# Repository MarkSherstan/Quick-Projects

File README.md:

# [Wiki](https://github.com/MarkSherstan/Quick-Projects/wiki)
Check out the [Wiki](https://github.com/MarkSherstan/Quick-Projects/wiki) for full details on this repository. 

If you plan on working offline consider cloning the wiki locally:
```
git clone https://github.com/MarkSherstan/Quick-Projects.wiki.git
```

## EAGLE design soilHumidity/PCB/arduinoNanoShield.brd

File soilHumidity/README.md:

# Soil Humidity Classifier for Home Plants
Program for determining the soil humidity levels in various house hold plants.

Also using the project to test the basic functionality of PlatformIO instead of Arduino IDE.

## Usage
Build and upload with PlatformIO or copy and paste `\src\main.cpp` excluding the `#include <Arduino.h>` header into Arduino IDE and compile as normal.

The 7 segment display values correspond to the relative humidity. For example 1 indicates 0-10% relative humidity, 2 indicates 10-20% relative humidity, etc... For greater than 90% relative humidity the decimal point will flash.

## Specs and Data Sheets
Sensor purchased from Banggood and came with the following information:

* Supply voltage: 3.3V or 5V
* Operating current: less than 20mA
* Output voltage: 0-2.3V (2.3V is completely immersed in water voltage value),
* 5V power supply, the greater the humidity, the greater the output voltage.
* Sensor type: Analog Output

## Case
The top of the case was modified from [this](https://www.thingiverse.com/thing:994827) model on Thingiverse. CAD files can be found in the `case` directory.  

## Wiring schematic

## Cover Photo

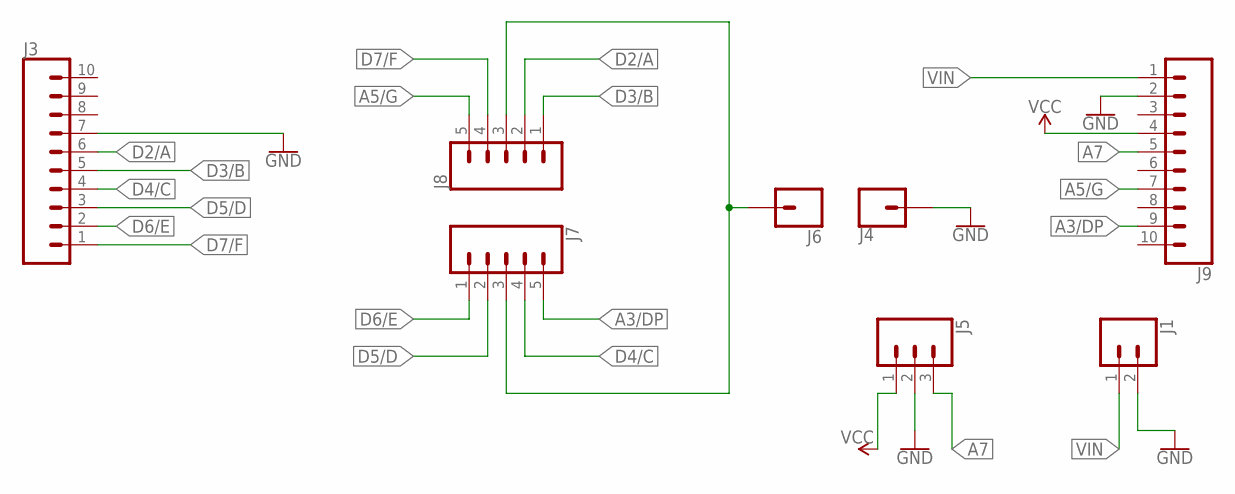
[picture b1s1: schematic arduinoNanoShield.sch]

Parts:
J1: CONN_02; 1X02
J3, J9: CONN_10"; 1X10
J4, J6: CONN_01; 1X01
J5: CONN_03; 1X03
J7, J8: CONN_05; 1X05

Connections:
A3/DP: J7.5, J9.9
A5/G: J8.5, J9.7
A7: J5.3, J9.5
D2/A: J3.6, J8.2
D3/B: J3.5, J8.1
D4/C: J3.4, J7.4
D5/D: J3.3, J7.2
D6/E: J3.2, J7.1
D7/F: J3.1, J8.4
GND: J1.2, J3.7, J4.1, J5.2, J9.2
unnamed: J6.1, J7.3, J8.3
VCC: J5.1, J9.4
VIN: J1.1, J9.1

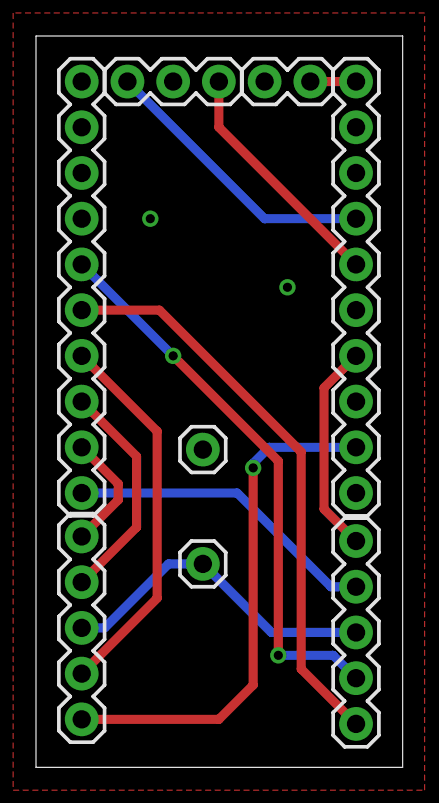
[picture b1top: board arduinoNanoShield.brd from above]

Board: 2 copper layers, 20.4 x 40.6 mm, 8 parts (0 on the bottom side), 13 nets.

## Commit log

2019-01-21 Commit PlatformIO root files
2019-01-21 Wrote initial framework of arduino sketch.
2019-01-21 Update README(s)
2019-01-21 Add second sensor and average results
2019-01-22 Fixed LED's from always staying on once activated by if statment.
2019-01-23 Initial commit wiring diagram
2019-01-23 Use one sensor and one LED and vary blinking speeds.
2019-01-26 Changed code to use 7 segment display instead of flashing LED
2019-01-26 Update wiring diagram for 7 seg display.
2019-01-26 Commit CAD files.
2019-01-26 Add cover photos
2019-01-26 Read add cover photos - HEIC format.
2019-01-26 Compress file size for cover photos.
2019-01-26 Remove HEIC, export .png, resize cover photos.
2019-01-26 Update README
    Change to HTML formatting from ![]()
2019-01-26 Update README
    Change from ![]() to HTML
2019-01-26 Change aspect ratio of cover photos
2019-01-27 Changed output for greater than 100% to be just a dot.
2019-02-15 Initial commit of sensor project code.
2019-02-18 Designed quick PCB to test othermill pro in engg garage.
2019-03-01 Initial commit for Arduino ESC calibration
2019-03-01 Initial commit of Arduino servo control using serial port.
2019-03-03 Initial commit for detecting mouse location to set up automater.
2019-03-04 Changed clicks to tabs for speed increase
2019-03-04 Created function for multiple entries
2019-03-04 Initial commit of README
2019-03-08 Initial commit real time plotter .m function.
2019-03-27 MATLAB and Arduino serial port communication. 45-50 Hz with MEGA2560.
2019-04-30 Initial commit - Slider for HSV colorspace and masking.
2019-05-01 Upload some test data
2019-05-02 Update background detection algorithm and laser tracking.
2019-05-02 Add the updated background and laser tracking to RPi code.
2019-05-02 Initial commit of C++ serial port reading.
2019-05-02 Initial commit of analog thermistor sensor.
2019-05-02 Initial commit of ultrasonic sensor
2019-05-17 Initial commit serialPython.py
2019-05-17 Initial commit C++ files for serial port.
2019-05-17 Initial commit arduinoSerial.ino
2019-05-17 Initial commit serialMatlab.m
2019-05-17 Commit MATLAB serial port reading (2 methods).
2019-05-17 Formatting update.
2019-06-01 Transition to windows and make user enter after every entry.
2019-09-30 Initial commit FSR sketch
2019-09-30 Add FSR-400 data sheet
2019-09-30 HX711 amplifier and load cell.
2019-09-30 Add README
2019-10-11 Fill out README
2019-10-12 Commit JSON parsing and dataframe work
2019-10-12 Commit gitignore for PNG's
2019-10-12 Tune some OCR and image processing properties.
2019-10-13 Only use one screen shot. Get rid of other functions for img processing.
2019-10-13 Make corresponding changes to JSON class
2019-10-13 Added comparison dataFrame columns and tidy up a few functions.
2019-10-13 Added some error handling.
2019-10-13 Commit example data and GAME_MASTER from october 11, 2019.
2019-10-13 Add file extension
2019-10-18 Initialize readme
2019-10-18 Commit calibration directory.
2019-10-18 Add first few functions for marker gen and calibration data gen.
2019-10-18 Commit calibration and retrieval function
2019-10-18 Added real time tracking.
2019-10-19 Add gitignore for images and pickles
2019-10-19 Debuging and testing.
2019-10-19 Commit main arduino sketch for servo control.
2019-10-19 Commit serial grabbing
2019-10-19 Add software reset inplace of hardware reset.
2019-10-19 Commit camera calibration
2019-10-19 Commit 9x6 chessboard pattern
2019-10-19 Update .gitignore for just calibration images.
2019-10-19 Commit open house working code
2019-10-20 Add aruco test images in new directory
2019-11-01 Fix blackscreen bug with error handling
2019-11-18 Add recording option
2019-12-17 Add some moveset optimization that is in the works.
2019-12-17 2 methods for tracking of laser.
2019-12-17 Commit alternative method
2019-12-19 Rename /37in1sensorKit directory to /miscArduinoSensors
2019-12-19 Clean up for consistency and ease of use while creating the wiki.
2019-12-19 Move README to the wiki and add a few comments for ease of use.
2019-12-19 rename MATLAB functions, scripts, and folders to follow the wiki.
2019-12-20 Remove unnecessary data and cleaned everything up into one file.
2019-12-20 Add extra comments for better transparency with the wiki.
2019-12-20 Clean up folder structure and increase code readability.
2019-12-23 Remove MATLAB serial port fncs and fix spacing.
2019-12-23 Remove README
2019-12-23 Remove laser tracker code. Will be added in its own branch later.
2019-12-25 Re-add laser tracker files removed earlier into proper branch.
2020-03-22 Working code for test data
2020-03-22 added USD and CAD error checking
2020-03-22 Added better instructions
2020-03-22 Add all test data and the resulting file
2020-03-29 Add short term debt and TTM
2020-03-29 update file paths and names for incoming financial data
2020-03-29 Financial data from balance sheet
2020-03-29 Minor tweak moving variables between key ratios and financials
2020-06-09 Update directory to ArUco-Claw
2020-06-09 Create seperate connectCamera function
2020-06-10 Commit calibration photos
2020-06-10 Camera calibration
2020-06-10 Change index for capture camera and getCal fnc
2020-06-10 Initial tests look good
2020-06-10 Compare rotation matrix formulation
2020-06-10 Update coordinate frames to NED
2020-06-10 Test image
2020-06-10 Update rotation matrix for NED
2020-06-10 Testing transformation matrices
2020-06-10 Convert to body frame and fix rpy
2020-06-10 Update camera to body frame coords
2020-06-10 All frames in correct orientation
2020-06-10 Final checks passed
2020-07-11 Add snap shot function
2020-07-12 Fix R to euler and set up some various frames
2020-07-17 Update calibration
2020-07-23 Clean up
2020-07-23 Clean up calibration
2020-07-24 Add OpenCV streamer
2021-12-04 Remove laser tracker
2021-12-04 Fix some spacing
2021-12-07 Tidy formatting and var names
2023-01-01 Update some cam settings

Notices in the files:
parts and their libraries:
SparkFun-Connectors: Licensing: Creative Commons ShareAlike 4.0 International - https://creativecommons.org/licenses/by-sa/4.0
